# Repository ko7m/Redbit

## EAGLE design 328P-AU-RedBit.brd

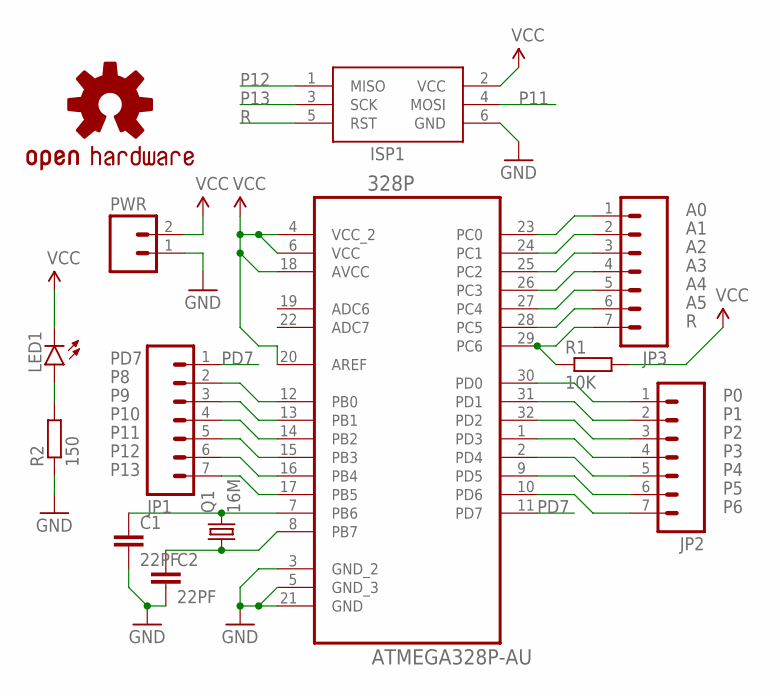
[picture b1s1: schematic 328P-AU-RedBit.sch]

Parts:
328P: ATMEGA328P-AU; QFP80P900X900X120-32N
C1, C2: 22PF; C0805
ISP1: AVRISP-6; AVRISP
JP1, JP2, JP3: M07; 1X07
LED1: LED0603; LED-0603
LOGO1: OSHW-LOGOS; OSHW-LOGO-S
PWR: M02PTH; 1X02
Q1: 16M; HC49/S
R1: 10K; R0805
R2: 150; R0805

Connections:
A0: 328P.23 (PC0), JP3.1
A1: 328P.24 (PC1), JP3.2
A2: 328P.25 (PC2), JP3.3
A3: 328P.26 (PC3), JP3.4
A4: 328P.27 (PC4), JP3.5
A5: 328P.28 (PC5), JP3.6
GND: 328P.3 (GND_2), 328P.5 (GND_3), 328P.21 (GND), C1.2, C2.2, ISP1.6 (GND), PWR.1, R2.1
unnamed: 328P.7 (PB6), C1.1, Q1.2
unnamed: 328P.8 (PB7), C2.1, Q1.1
unnamed: LED1.A, R2.2
P0: 328P.30 (PD0), JP2.1
P1: 328P.31 (PD1), JP2.2
P2: 328P.32 (PD2), JP2.3
P3: 328P.1 (PD3), JP2.4
P4: 328P.2 (PD4), JP2.5
P5: 328P.9 (PD5), JP2.6
P6: 328P.10 (PD6), JP2.7
P8: 328P.12 (PB0), JP1.2
P9: 328P.13 (PB1), JP1.3
P10: 328P.14 (PB2), JP1.4
P11: 328P.15 (PB3), ISP1.4 (MOSI), JP1.5
P12: 328P.16 (PB4), ISP1.1 (MISO), JP1.6
P13: 328P.17 (PB5), ISP1.3 (SCK), JP1.7
PD7: 328P.11 (PD7), JP1.1
R: 328P.29 (PC6), ISP1.5 (RST), JP3.7, R1.1
VCC: 328P.4 (VCC_2), 328P.6 (VCC), 328P.18 (AVCC), 328P.20 (AREF), ISP1.2 (VCC), LED1.C, PWR.2, R1.2

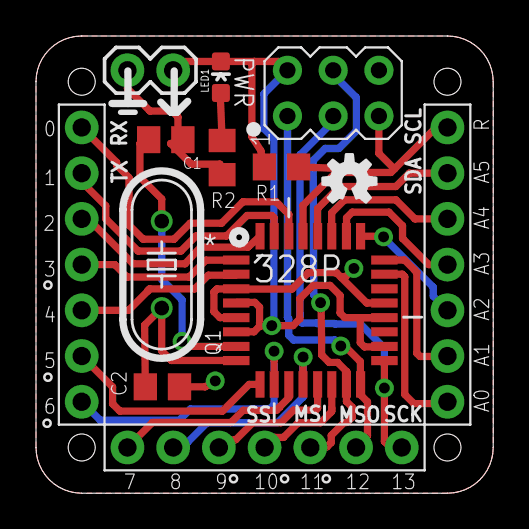
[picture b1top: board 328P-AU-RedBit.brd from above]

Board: 2 copper layers, 25.4 x 25.4 mm, 13 parts (0 on the bottom side), 26 nets.

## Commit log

2015-05-08 :space_invader: Added .gitattributes
2015-05-17 added files
2015-06-03 add png

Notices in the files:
parts and their libraries:
SparkFun-Connectors: Licensing: Creative Commons ShareAlike 4.0 International - https://creativecommons.org/licenses/by-sa/4.0
